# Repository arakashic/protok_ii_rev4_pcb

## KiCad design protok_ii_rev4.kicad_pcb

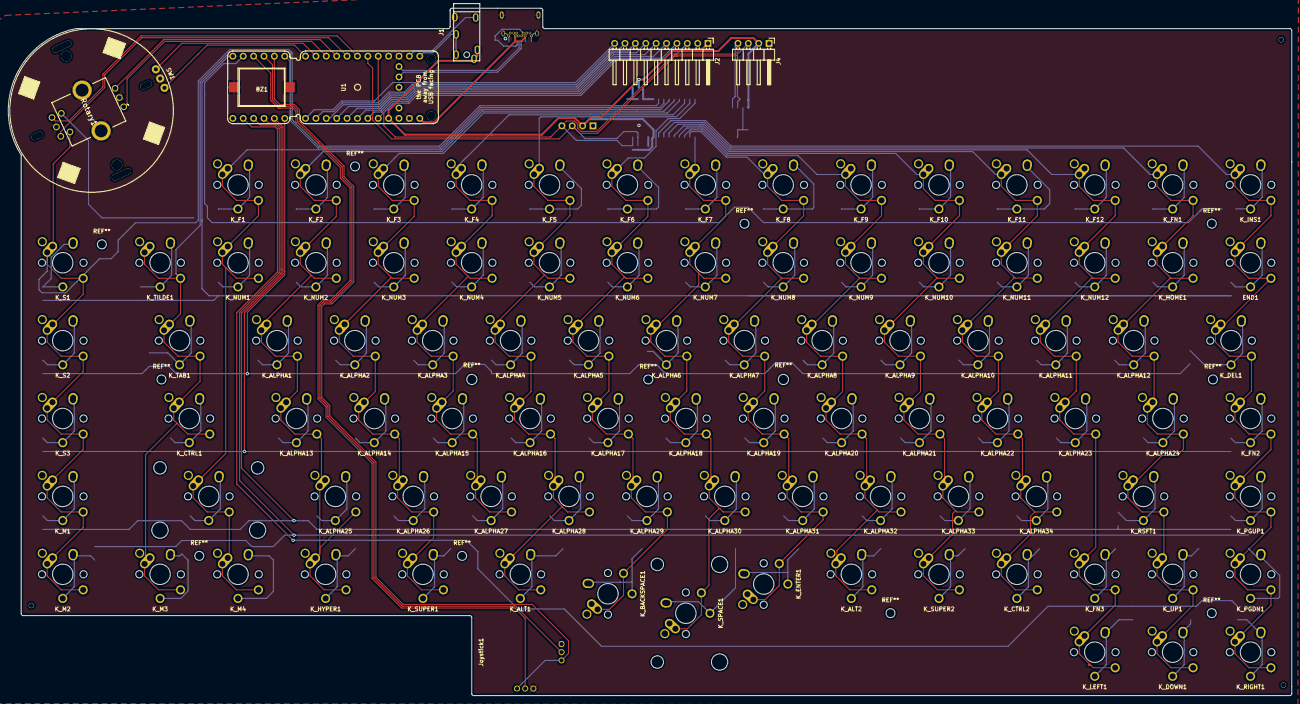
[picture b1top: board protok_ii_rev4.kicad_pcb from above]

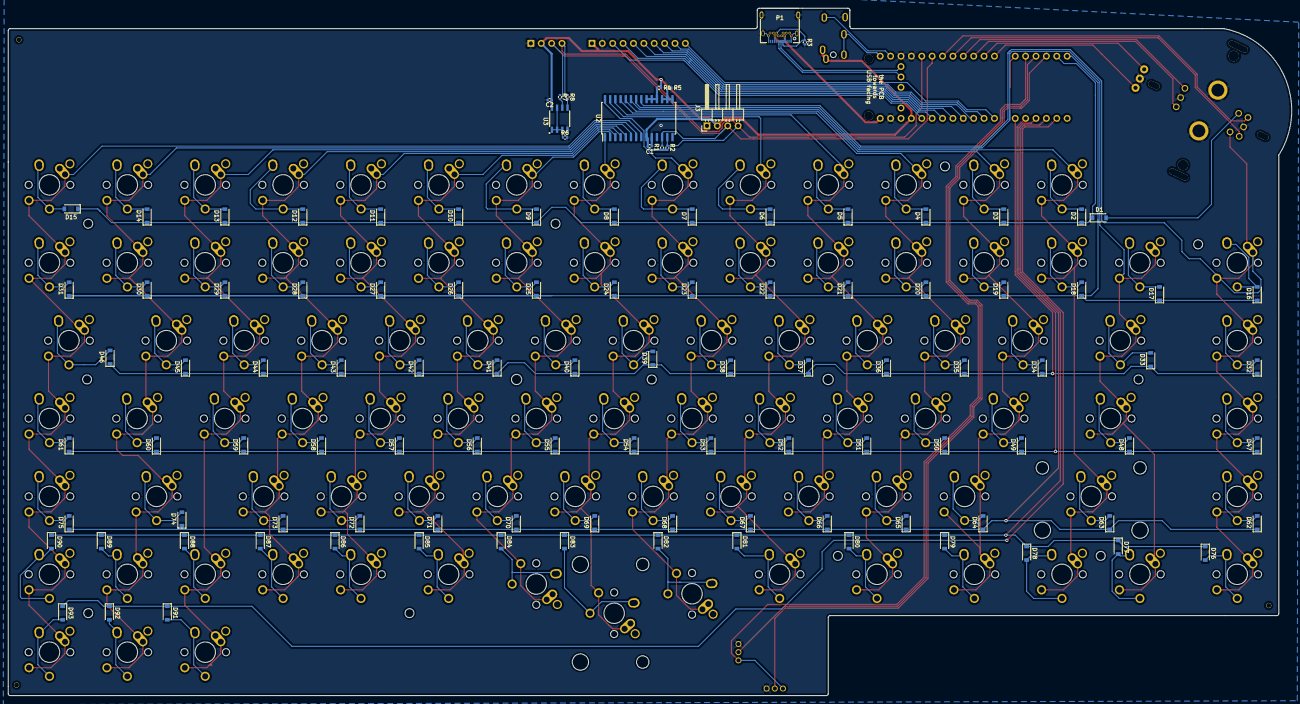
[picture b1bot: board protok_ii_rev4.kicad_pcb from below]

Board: 2 copper layers, 313.9 x 168.1 mm, 207 parts (107 on the bottom side), 147 nets.

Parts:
BZ1: Buzzer; AST1109MLTRQ
C1, C2: 100nF; C_0402_1005Metric
D1, D2, D3, D4, D5, D6, D7, D8, D9, D10, D11, D12, D13, D14, D15, D16, D17, D18, D19, D20, D21, D22, D23, D24, D25, D26, D27, D28, D29, D30, D31, D32, D33, D34, D35, D36, D37, D38, D39, D40, D41, D42, D43, D44, D45, D46, D47, D48, D49, D50, D51, D52, D53, D54, D55, D56, D57, D58, D59, D60, D61, D62, D63, D64, D65, D66, D67, D68, D69, D70, D71, D72, D73, D74, D75, D76, D77, D78, D79, D80, D81, D82, D83, D84, D85, D86, D87, D88, D89, D90, D91, D92, D93: 1N4148; D_SOD-123
END1: MX-NoLED; MX-1U
J1: AudioPlug4; 3.5mm_phone_jack_THT
J2: Conn_01x10_Male; PinHeader_1x10_P2.54mm_Horizontal
J3, J4: Conn_01x04_Male; PinHeader_1x04_P2.54mm_Horizontal
Joystick1: 2_axis_thumbstick
K_ALPHA1, K_ALPHA2, K_ALPHA3, K_ALPHA4, K_ALPHA5, K_ALPHA6, K_ALPHA7, K_ALPHA8, K_ALPHA9, K_ALPHA10, K_ALPHA11, K_ALPHA12, K_ALPHA13, K_ALPHA14, K_ALPHA15, K_ALPHA16, K_ALPHA17, K_ALPHA18, K_ALPHA19, K_ALPHA20, K_ALPHA21, K_ALPHA22, K_ALPHA23, K_ALPHA25, K_ALPHA26, K_ALPHA27, K_ALPHA28, K_ALPHA29, K_ALPHA30, K_ALPHA31, K_ALPHA32, K_ALPHA33, K_ALPHA34: MX-NoLED; MX-1U
K_ALPHA24: MX-NoLED; MX-1.25U
K_ALT1, K_ALT2: MX-NoLED; MX-1.25U
K_BACKSPACE1: MX-NoLED; MX-1.5U
K_CTRL1: MX-NoLED; MX-1.75U
K_CTRL2: MX-NoLED; MX-1U
K_DEL1: MX-NoLED; MX-1.5U
K_DOWN1: MX-NoLED; MX-1U
K_ENTER1: MX-NoLED; MX-1.25U
K_F1, K_F2, K_F3, K_F4, K_F5, K_F6, K_F7, K_F8, K_F9, K_F10, K_F11, K_F12: MX-NoLED; MX-1U
K_FN1, K_FN2, K_FN3: MX-NoLED; MX-1U
K_HOME1: MX-NoLED; MX-1U
K_HYPER1: MX-NoLED; MX-1.25U
K_INS1: MX-NoLED; MX-1U
K_LEFT1: MX-NoLED; MX-1U
K_LSFT1: MX-NoLED; MX-2.25U
K_M1, K_M2, K_M3, K_M4: MX-NoLED; MX-1U
K_NUM1, K_NUM2, K_NUM3, K_NUM4, K_NUM5, K_NUM6, K_NUM7, K_NUM8, K_NUM9, K_NUM10, K_NUM11, K_NUM12: MX-NoLED; MX-1U
K_PGDN1: MX-NoLED; MX-1U
K_PGUP1: MX-NoLED; MX-1U
K_RIGHT1: MX-NoLED; MX-1U
K_RSFT1: MX-NoLED; MX-1.75U
K_S1, K_S2, K_S3: MX-NoLED; MX-1U
K_SPACE1: MX-NoLED; MX-2U
K_SUPER1: MX-NoLED; MX-1.25U
K_SUPER2: MX-NoLED; MX-1U
K_TAB1: MX-NoLED; MX-1.5U
K_TILDE1: MX-NoLED; MX-1U
K_UP1: MX-NoLED; MX-1U
P1: USB_C_Plug; TYPE-C-31-M-04
R1, R2, R4, R5, R6, R7, R8: 10K; R_0402_1005Metric
R3: 5.1K; R_0402_1005Metric
Rotary1: EC11EBB24C03
SW1: Rotary_Encoder; EC35A1520402
U1: proton_c
U2: MCP23017_SO; SOIC-28W_7.5x17.9mm_P1.27mm
U3: AT24C256C-SSHL-B; SOIC127P600X175-8N

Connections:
+3V3: C1.1, C2.1, J1.S, J2.1, J3.2, J4.2, R1.1, R2.1, R4.2, U1.3.3V, U2.9, U3.8
A0: J2.5, U1.A0
A1: Rotary1.A1, U1.B2
A2: Rotary1.A2, U1.B4
A3: SW1.A, U1.B0
B1: Rotary1.B1, U1.B3
B2: Rotary1.B2, U1.B5
B3: SW1.B, U1.B1
B8: J2.6, U1.B8
B9: J2.10, U1.B9
Col0: K_M1.1, K_M2.1, K_S1.1, K_S2.1, K_S3.1, Rotary1.D1, U2.21
Col1: K_CTRL1.1, K_M3.1, K_TAB1.1, K_TILDE1.1, U2.22
Col2: K_F1.1, K_LSFT1.1, K_M4.1, K_NUM1.1, U2.23
Col3: K_ALPHA1.1, K_ALPHA13.1, K_ALPHA25.1, K_F2.1, K_HYPER1.1, K_NUM2.1, U2.24
Col4: K_ALPHA2.1, K_ALPHA14.1, K_ALPHA26.1, K_F3.1, K_NUM3.1, K_SUPER1.1, U2.25
Col5: K_ALPHA3.1, K_ALPHA15.1, K_ALPHA27.1, K_F4.1, K_NUM4.1, U2.26
Col6: K_ALPHA4.1, K_ALPHA16.1, K_ALPHA28.1, K_ALT1.1, K_F5.1, K_NUM5.1, U2.27
Col7: K_ALPHA5.1, K_ALPHA17.1, K_ALPHA29.1, K_BACKSPACE1.1, K_F6.1, K_NUM6.1, U2.28
Col8: K_ALPHA6.1, K_ALPHA18.1, K_ALPHA30.1, K_F7.1, K_NUM7.1, K_SPACE1.1, U2.1
Col9: K_ALPHA7.1, K_ALPHA19.1, K_ALPHA31.1, K_ENTER1.1, K_F8.1, K_NUM8.1, U2.2
Col10: K_ALPHA8.1, K_ALPHA20.1, K_ALPHA32.1, K_ALT2.1, K_F9.1, K_NUM9.1, U2.3
Col11: K_ALPHA9.1, K_ALPHA21.1, K_ALPHA33.1, K_F10.1, K_NUM10.1, K_SUPER2.1, U2.4
Col12: K_ALPHA10.1, K_ALPHA22.1, K_ALPHA34.1, K_CTRL2.1, K_F11.1, K_NUM11.1, U2.5
Col13: K_ALPHA11.1, K_ALPHA23.1, K_F12.1, K_FN3.1, K_LEFT1.1, K_NUM12.1, U2.6
Col14: K_ALPHA12.1, K_ALPHA24.1, K_DOWN1.1, K_FN1.1, K_HOME1.1, K_RSFT1.1, K_UP1.1, U2.7
Col15: END1.1, K_DEL1.1, K_FN2.1, K_INS1.1, K_PGDN1.1, K_PGUP1.1, K_RIGHT1.1, U2.8
D+: P1.A6, U1.D+
D-: P1.A7, U1.D-
GND: BZ1.2, C1.2, C2.2, J1.T, J2.2, J3.1, J4.1, Joystick1.3, Joystick1.6, P1.A1, P1.A12, P1.B1, P1.B12, P1.S1, R3.2, R5.2, R6.2, Rotary1.C1, Rotary1.C2, Rotary1.MH1, Rotary1.MH2, SW1.C, U1.GND, U2.10, U3.4
J_EN: Joystick1.1, Joystick1.4, U1.A5
MISO: J2.8, U1.B14
MOSI: J2.9, U1.B15
unnamed: D1.2, Rotary1.E1
unnamed: D2.2, K_F1.2
unnamed: D3.2, K_F2.2
unnamed: D4.2, K_F3.2
unnamed: D5.2, K_F4.2
unnamed: D6.2, K_F5.2
unnamed: D7.2, K_F6.2
unnamed: D8.2, K_F7.2
unnamed: D9.2, K_F8.2
unnamed: D10.2, K_F9.2
unnamed: D11.2, K_F10.2
unnamed: D12.2, K_F11.2
unnamed: D13.2, K_F12.2
unnamed: D14.2, K_FN1.2
unnamed: D15.2, K_INS1.2
unnamed: D16.2, K_S1.2
unnamed: D17.2, K_TILDE1.2
unnamed: D18.2, K_NUM1.2
unnamed: D19.2, K_NUM2.2
unnamed: D20.2, K_NUM3.2
unnamed: D21.2, K_NUM4.2
unnamed: D22.2, K_NUM5.2
unnamed: D23.2, K_NUM6.2
unnamed: D24.2, K_NUM7.2
unnamed: D25.2, K_NUM8.2
unnamed: D26.2, K_NUM9.2
unnamed: D27.2, K_NUM10.2
unnamed: D28.2, K_NUM11.2
unnamed: D29.2, K_NUM12.2
unnamed: D30.2, K_HOME1.2
unnamed: D31.2, END1.2
unnamed: D32.2, K_S2.2
unnamed: D33.2, K_TAB1.2
unnamed: D34.2, K_ALPHA1.2
unnamed: D35.2, K_ALPHA2.2
unnamed: D36.2, K_ALPHA3.2
unnamed: D37.2, K_ALPHA4.2
unnamed: D38.2, K_ALPHA5.2
unnamed: D39.2, K_ALPHA6.2
unnamed: D40.2, K_ALPHA7.2
unnamed: D41.2, K_ALPHA8.2
unnamed: D42.2, K_ALPHA9.2
unnamed: D43.2, K_ALPHA10.2
unnamed: D44.2, K_ALPHA11.2
unnamed: D45.2, K_ALPHA12.2
unnamed: D46.2, K_DEL1.2
unnamed: D47.2, K_S3.2
unnamed: D48.2, K_CTRL1.2
unnamed: D49.2, K_ALPHA13.2
unnamed: D50.2, K_ALPHA14.2
unnamed: D51.2, K_ALPHA15.2
unnamed: D52.2, K_ALPHA16.2
unnamed: D53.2, K_ALPHA17.2
unnamed: D54.2, K_ALPHA18.2
unnamed: D55.2, K_ALPHA19.2
unnamed: D56.2, K_ALPHA20.2
unnamed: D57.2, K_ALPHA21.2
unnamed: D58.2, K_ALPHA22.2
unnamed: D59.2, K_ALPHA23.2
unnamed: D60.2, K_ALPHA24.2
unnamed: D61.2, K_FN2.2
unnamed: D62.2, K_M1.2
unnamed: D63.2, K_LSFT1.2
unnamed: D64.2, K_ALPHA25.2
unnamed: D65.2, K_ALPHA26.2
unnamed: D66.2, K_ALPHA27.2
unnamed: D67.2, K_ALPHA28.2
unnamed: D68.2, K_ALPHA29.2
unnamed: D69.2, K_ALPHA30.2
unnamed: D70.2, K_ALPHA31.2
unnamed: D71.2, K_ALPHA32.2
unnamed: D72.2, K_ALPHA33.2
unnamed: D73.2, K_ALPHA34.2
unnamed: D74.2, K_RSFT1.2
unnamed: D75.2, K_PGUP1.2
unnamed: D76.2, K_M2.2
unnamed: D77.2, K_M3.2
unnamed: D78.2, K_M4.2
unnamed: D79.2, K_HYPER1.2
unnamed: D80.2, K_SUPER1.2
unnamed: D81.2, K_ALT1.2
unnamed: D82.2, K_BACKSPACE1.2
unnamed: D83.2, K_SPACE1.2
unnamed: D84.2, K_ENTER1.2
unnamed: D85.2, K_ALT2.2
unnamed: D86.2, K_SUPER2.2
unnamed: D87.2, K_CTRL2.2
unnamed: D88.2, K_FN3.2
unnamed: D89.2, K_UP1.2
unnamed: D90.2, K_PGDN1.2
unnamed: D91.2, K_LEFT1.2
unnamed: D92.2, K_DOWN1.2
unnamed: D93.2, K_RIGHT1.2
unnamed: P1.A5, P1.B5, R3.1
unnamed: R4.1, U2.18, U2.19, U2.20
unnamed: R5.1, U2.15, U2.16, U2.17
unnamed: R6.1, U3.1, U3.2, U3.3, U3.7
RX: J1.R1, U1.A10
Row0: D1.1, D2.1, D3.1, D4.1, D5.1, D6.1, D7.1, D8.1, D9.1, D10.1, D11.1, D12.1, D13.1, D14.1, D15.1, U1.A8
Row1: D16.1, D17.1, D18.1, D19.1, D20.1, D21.1, D22.1, D23.1, D24.1, D25.1, D26.1, D27.1, D28.1, D29.1, D30.1, D31.1, U1.A15
Row2: D32.1, D33.1, D34.1, D35.1, D36.1, D37.1, D38.1, D39.1, D40.1, D41.1, D42.1, D43.1, D44.1, D45.1, D46.1, U1.B10
Row3: D47.1, D48.1, D49.1, D50.1, D51.1, D52.1, D53.1, D54.1, D55.1, D56.1, D57.1, D58.1, D59.1, D60.1, D61.1, U1.B11
Row4: D62.1, D63.1, D64.1, D65.1, D66.1, D67.1, D68.1, D69.1, D70.1, D71.1, D72.1, D73.1, D74.1, D75.1, U1.B12
Row5: D76.1, D77.1, D78.1, D79.1, D80.1, D81.1, D82.1, D83.1, D84.1, D85.1, D86.1, D87.1, D88.1, D89.1, D90.1, U1.A14
Row6: D91.1, D92.1, D93.1, U1.A13
SA1: J2.4, U1.A1
SA2: J2.3, U1.A2
SCL: J3.3, J4.3, R1.2, R7.2, U1.B6, U2.12, U3.6
SCLK: J2.7, U1.B13
SDA: J3.4, J4.4, R2.2, R8.2, U1.B7, U2.13, U3.5
SPK: BZ1.1, U1.A4
TX: J1.R2, U1.A9
VBUS: P1.A4, P1.A9, P1.B4, P1.B9, U1.5V
X1: Joystick1.2, U1.A7
Y1: Joystick1.5, U1.A6

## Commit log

2021-04-23 initial import
2021-08-27 library: add footprint for EC35 and MKI2C
2021-08-27 update submodule
2021-08-27 update schematic
2021-08-27 update component
2021-09-11 update library
2021-09-11 ignore gerber file
2021-09-11 finish pcb
2021-09-12 add eeprom
2021-09-12 final version with eeprom
2021-09-18 add manufacturing file
2022-07-16 add keebio-parts
2022-07-16 rename to rev4
2022-07-16 convert to kicad 6
2022-07-24 update design
2022-07-24 ignore backup files
